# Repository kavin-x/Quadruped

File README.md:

# 🐕 In-House High-Performance Quadruped Robot

## 📌 Project Overview

This project focuses on the design and development of a **high-performance quadruped robotic dog**, built entirely in-house with a strong emphasis on modularity, efficiency, and scalability.

The system is built around custom motor control electronics using the **STM32G431CBU6** microcontroller, implementing advanced **Field Oriented Control (FOC)** and real-time **CAN FD communication** between joints.

Our goal is to design and develop every critical subsystem internally — including actuator electronics, firmware architecture, communication stack, and mechanical integration.

---

## 🎯 Objectives

- Develop high-efficiency FOC-based motor control
- Design modular smart actuators
- Implement deterministic real-time CAN FD communication
- Build scalable firmware architecture for multi-joint control
- Optimize for performance, responsiveness, and energy efficiency
- Maintain complete in-house system ownership and understanding

---

## 🧠 System Architecture

### 🔹 Control Electronics
- Microcontroller: STM32G431CBU6
- Advanced timer-based PWM generation
- Inline / low-side current sensing
- High-speed ADC sampling
- CAN FD communication interface

### 🔹 Motor Control
- Field Oriented Control (FOC)
- High switching frequency PWM
- Real-time current control loop
- Velocity and position control loops
- Optimized for low latency and high torque response

### 🔹 Communication
- CAN FD based multi-node architecture
- Deterministic joint-level communication
- Scalable bus structure for 12+ actuators
- Distributed-ready control design

### 🔹 Mechanical Design
- Modular actuator units
- Custom motor driver PCB
- Compact, serviceable architecture
- Strength-to-weight optimized structure

---

## 📂 Repository Structure
/firmware
/motor_control
/can_fd
/drivers
/middleware

/hardware
/pcb_design
/schematics
/bom

/mechanical
/cad_files
/actuator_design

/docs
/progress_reports
/architecture_notes

---

## 🚀 Current Progress

- ✅ Custom motor driver PCB designed
- ✅ STM32G431 bring-up completed
- ✅ PWM generation validated
- ✅ ADC sampling verified
- ✅ Initial FOC implementation tested
- 🔄 CAN FD communication framework in progress
- 🔄 Multi-joint synchronization under development
- 🔄 Actuator mechanical refinement ongoing

---

## 🔜 Next Steps

- Complete closed-loop position control
- Optimize FOC loop timing and stability
- Finalize CAN FD protocol structure
- Integrate multiple actuators
- Begin quadruped gait testing
- Implement high-level motion control layer

---

## 🛠️ Development Tools

- STM32CubeIDE
- STM32 HAL / LL Drivers
- Custom FOC algorithms
- Oscilloscope and logic analyzer for validation
- CAN FD debugging tools

---

## 📈 Long-Term Vision

- Fully autonomous quadruped platform
- Advanced locomotion algorithms
- Real-time state estimation
- AI-assisted gait optimization
- Expandable research and development platform

---

## 🤝 Contribution

This is currently an in-house development project.  
Documentation and structured releases will be improved progressively.

---

## 📜 License

License information will be added soon.

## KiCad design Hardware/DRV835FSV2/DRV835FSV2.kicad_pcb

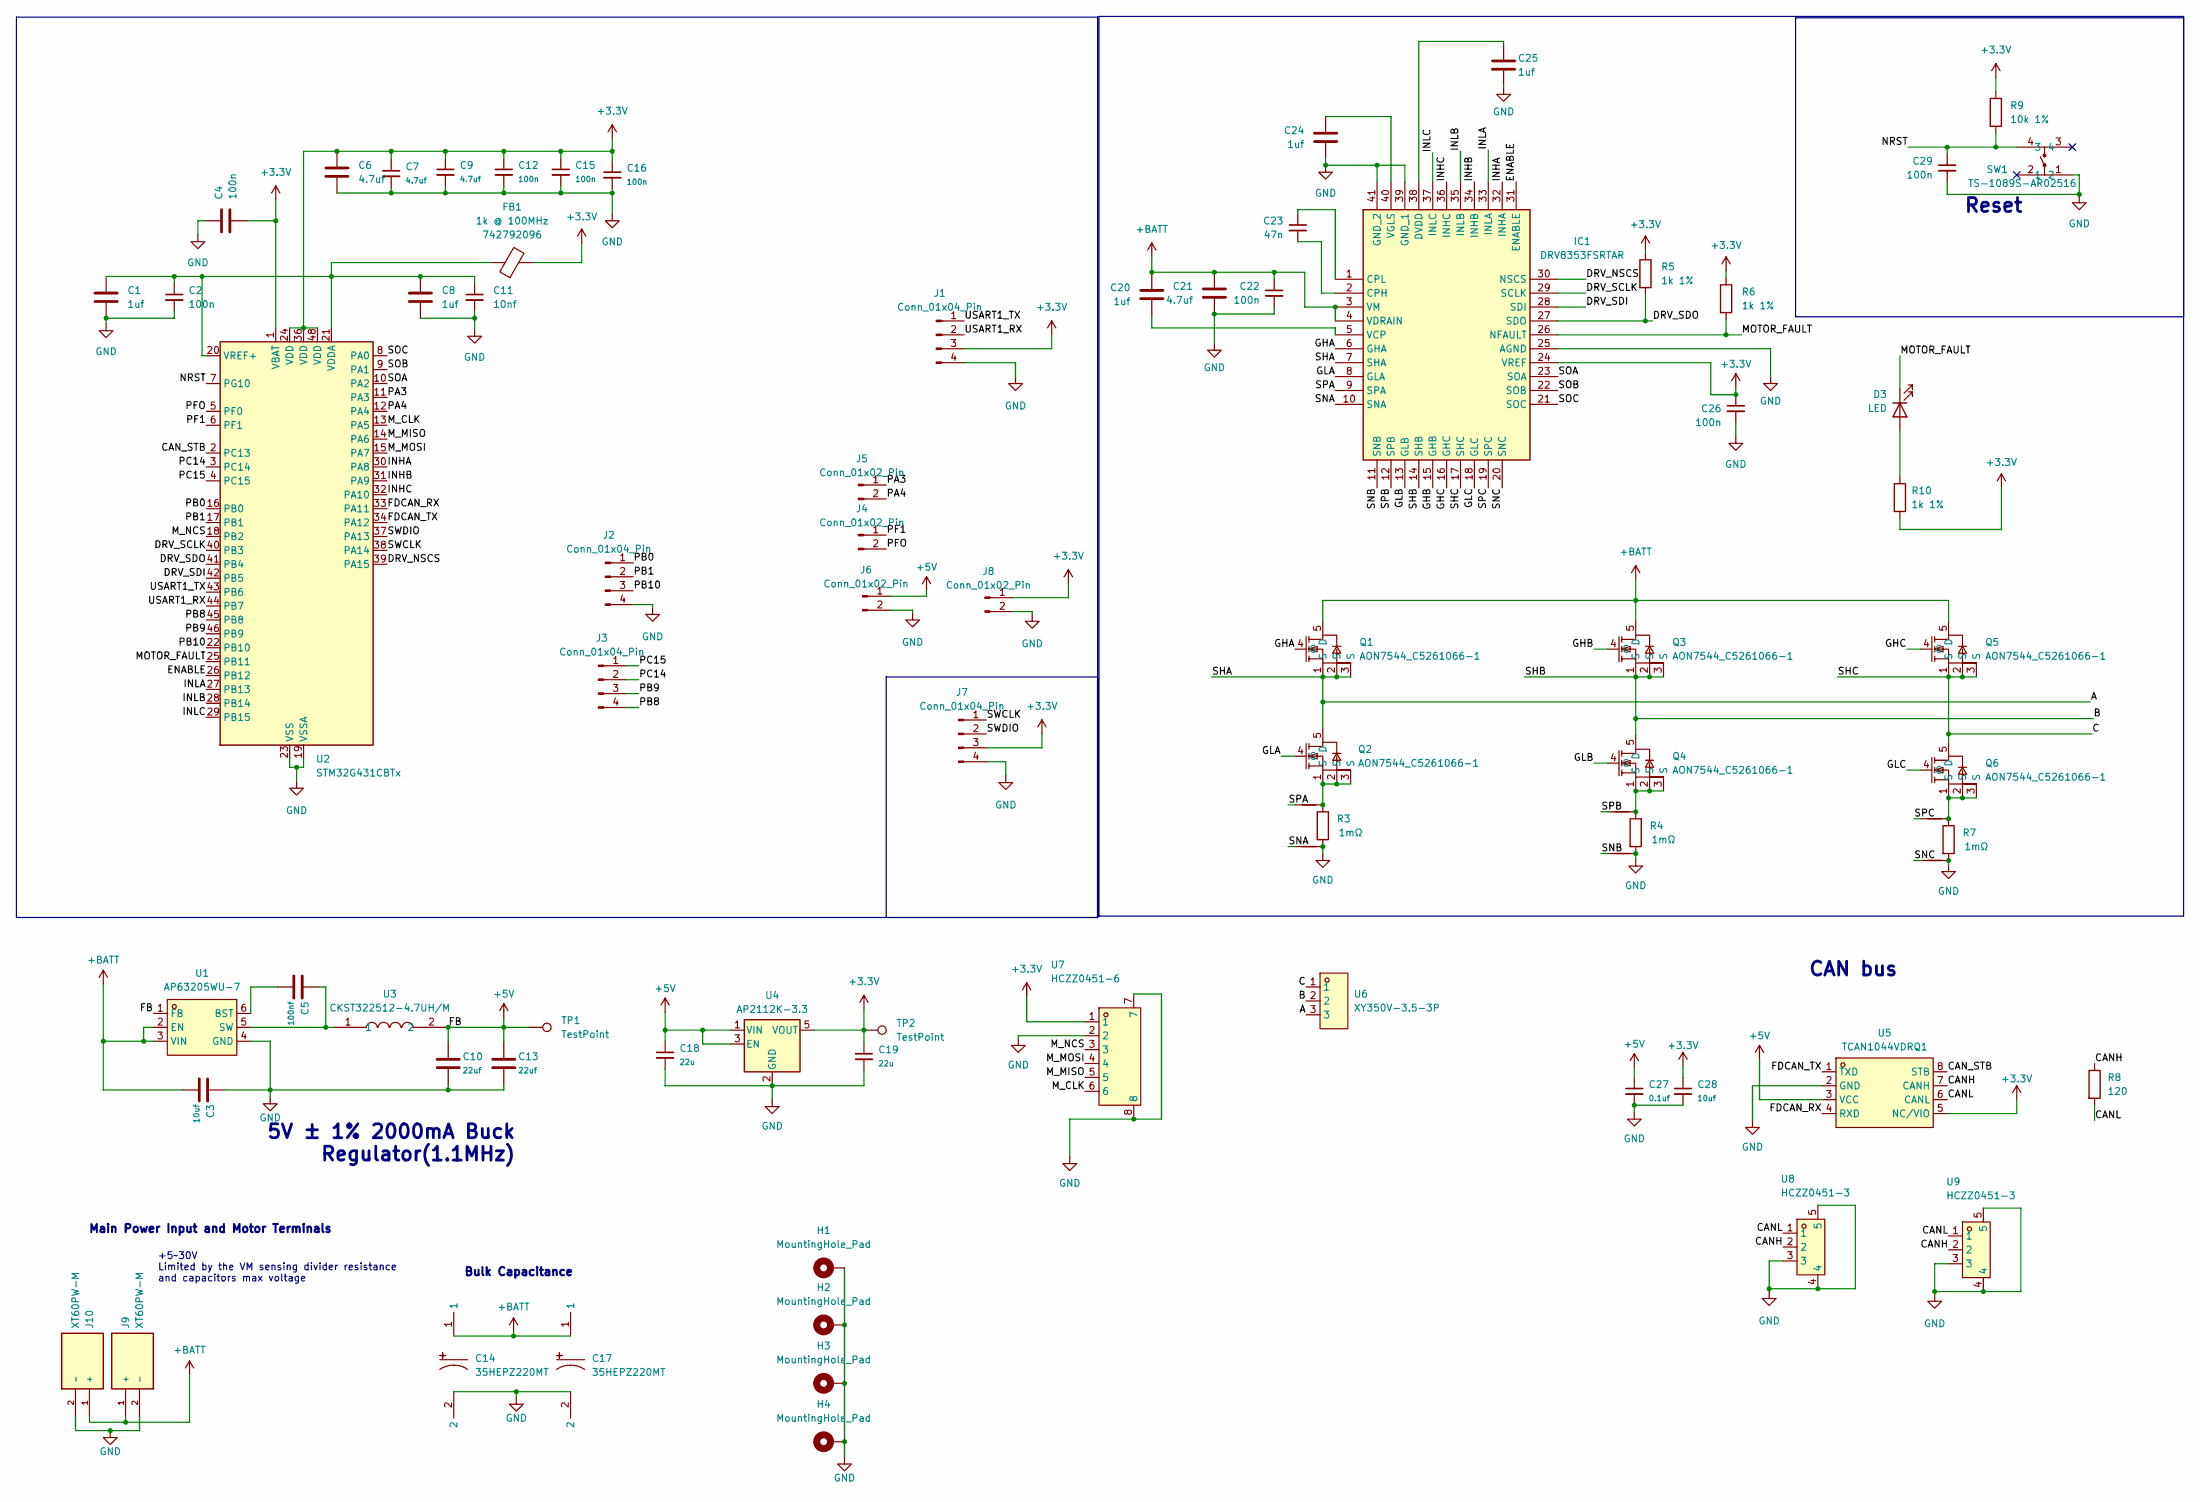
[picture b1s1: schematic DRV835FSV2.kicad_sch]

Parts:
C1: 1uf; C_0603_1608Metric; Manufacturer Part Number 04023D475MAT2A
C2, C12, C15, C16: 100n; C_0603_1608Metric; Manufacturer Part Number GCM155R71H104KE02J
C3: 10uf; C_0603_1608Metric; Manufacturer Part Number CGA4J1X7R2A225K125AC
C4: 100n; C_0603_1608Metric; Manufacturer Part Number GRM155Z71A105KE01J
C5: 100nf; C_0603_1608Metric; Manufacturer Part Number CGA4J1X7R2A225K125AC
C6: 4.7uf; C_0603_1608Metric; Manufacturer Part Number GRM188Z71C475KE21J
C7, C9: 4.7uf; C_0603_1608Metric; Manufacturer Part Number GCM155R71H104KE02J
C8: 1uf; C_0603_1608Metric; Manufacturer Part Number GRM155Z71A105KE01J
C10: 22uf; C_0603_1608Metric; Manufacturer Part Number GCM155R71H104KE02J
C11: 10nf; C_0603_1608Metric; Manufacturer Part Number GCM155R71H104KE02J
C13: 22uf; C_0603_1608Metric; Manufacturer Part Number GRM21BZ71A226ME15L
C14, C17: 35HEPZ220MT; CAP-TH_BD10.0-P5.00-D1.0-FD; LCSC Part C242064
C18, C19: 22u; C_0603_1608Metric; Manufacturer Part Number GCM155R71H104KE02J
C20, C24: 1uf; C_0603_1608Metric; Manufacturer Part Number TMK107AB7105KAHT
C21: 4.7uf; C_1206_3216Metric; Manufacturer Part Number GRJ31CZ72A475KE01L
C22: 100n; C_0603_1608Metric; Manufacturer Part Number HMK107B7104KAHT
C23: 47n; C_0603_1608Metric; Manufacturer Part Number C0603C473K1RECAUTO
C25: 1uf; C_0603_1608Metric; Manufacturer Part Number GRT155R70J105KE01D
C26: 100n; C_0603_1608Metric; Manufacturer Part Number GCM155R71C104KA55D
C27: 0.1uf; C_0603_1608Metric; Manufacturer Part Number GCM155R71H104KE02J
C28: 10uf; C_0603_1608Metric; Manufacturer Part Number GCM155R71H104KE02J
C29: 100n; C_0603_1608Metric; Manufacturer Part Number C0603C473K1RECAUTO
D3: LED; C_0603_1608Metric
FB1: 1k @ 100MHz; R_0603_1608Metric_Pad0.98x0.95mm_HandSolder; Manufacturer Part Number 742792096; LCSC Part C85824
H1, H2, H3, H4: MountingHole_Pad; MountingHole_2.7mm_Pad_Via
IC1: DRV8353FSRTAR; WQFN-40_L6.0-W6.0-P0.50-TL-EP4.5; Manufacturer_Part_Number DRV8353FSRTAR; Mouser Part Number 595-DRV8353FSRTAR
J1, J2, J3, J7: Conn_01x04_Pin; PinHeader_1x04_P2.54mm_Vertical
J4, J5, J6, J8: Conn_01x02_Pin; PinHeader_1x02_P2.54mm_Vertical
J9, J10: XT60PW-M; AMASS_XT60PW-M; PARTREV V1.2
NT1, NT2, NT3, NT4, NT5, NT6: NetTie_2; NetTie-2_SMD_Pad0.5mm
Q1, Q2, Q3, Q4, Q5, Q6: AON7544_C5261066-1; POWERDI3333-8_L3.3-W3.3-P0.65-BL; LCSC Part C5261066
R3, R4, R7: 1mΩ; R_2512_6332Metric; MFR.Part # ASR-M-3-0.5F; JLCPCB Part # C469426
R5, R6: 1k 1%; R_0603_1608Metric; Manufacturer Part Number ERJ-2RKF2001X; LCSC Part C21190
R8: 120; R_0603_1608Metric; Manufacturer Part Number ERJ-2RKF2001X; LCSC Part C21190
R9: 10k 1%; R_0603_1608Metric; Manufacturer Part Number ERJ-2RKF2001X; LCSC Part C25804
R10: 1k 1%; R_0603_1608Metric; Manufacturer Part Number ERJ-2RKF2001X; LCSC Part C25804
SW1: TS-1089S-AR02516; SW-SMD_4P-L4.2-W3.3-P2.15-LS5.1; LCSC Part C720479
TP1, TP2: TestPoint; TestPoint_Pad_D1.0mm
U1: AP63205WU-7; TSOT-23-6_L2.9-W1.6-P0.95-LS2.8-BL; LCSC Part C2071056
U2: STM32G431CBTx; LQFP-48_7x7mm_P0.5mm; LCSC Part C529355
U3: CKST322512-4.7UH/M; MGAH06034R7M-10; LCSC Part C3002560
U4: AP2112K-3.3; SOT-23-5; LCSC Part C51118
U5: TCAN1044VDRQ1; SOIC-8_L4.9-W3.9-P1.27-LS6.0-BL; LCSC Part C1852061
U6: XY350V-3.5-3P; CONN-TH_XY350V-3.5-3P; LCSC Part C557655
U7: HCZZ0451-6; CONN-SMD_HCZZ0451-6; LCSC Part C7433652
U8, U9: HCZZ0451-3; CONN-SMD_3P-P2.00_HCZZ0451-3_1; LCSC Part C7433649

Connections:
+3.3V: C4.2, C6.1, C7.1, C9.1, C12.1, C15.1, C16.1, C19.1, C26.1, C28.1, FB1.2, IC1.24 (VREF), J1.3, J7.3, J8.1, R5.1, R6.1, R9.1, R10.2, TP2.1, U2.1 (VBAT), U2.24 (VDD), U2.36 (VDD), U2.48 (VDD), U4.5 (VOUT), U5.5 (NC/VIO), U7.1
+5V: C10.1, C13.1, C18.1, C27.1, J6.1, TP1.1, U1.1 (FB), U3.2, U4.1 (VIN), U4.3 (EN), U5.3 (VCC)
+BATT: C3.2, C14.1, C17.1, C20.1, C21.1, C22.1, IC1.3 (VM), IC1.4 (VDRAIN), J9.1 (+), J10.1 (+), Q1.5 (D), Q3.5 (D), Q5.5 (D), U1.2 (EN), U1.3 (VIN)
/A: IC1.7 (SHA), Q1.1 (S), Q1.2 (S), Q1.3 (S), Q2.5 (D), U6.3
/B: IC1.14 (SHB), Q3.1 (S), Q3.2 (S), Q3.3 (S), Q4.5 (D), U6.2
/C: IC1.17 (SHC), Q5.1 (S), Q5.2 (S), Q5.3 (S), Q6.5 (D), U6.1
/CANH: R8.1, U5.7 (CANH), U8.2, U9.2
/CANL: R8.2, U5.6 (CANL), U8.1, U9.1
/CAN_STB: U2.2 (PC13), U5.8 (STB)
/DRV_NSCS: IC1.30 (NSCS), U2.39 (PA15)
/DRV_SCLK: IC1.29 (SCLK), U2.40 (PB3)
/DRV_SDI: IC1.28 (SDI), U2.42 (PB5)
/DRV_SDO: IC1.27 (SDO), R5.2, U2.41 (PB4)
/ENABLE: IC1.31 (ENABLE), U2.26 (PB12)
/FDCAN_RX: U2.33 (PA11), U5.4 (RXD)
/FDCAN_TX: U2.34 (PA12), U5.1 (TXD)
/GHA: IC1.6 (GHA), Q1.4 (G)
/GHB: IC1.15 (GHB), Q3.4 (G)
/GHC: IC1.16 (GHC), Q5.4 (G)
/GLA: IC1.8 (GLA), Q2.4 (G)
/GLB: IC1.13 (GLB), Q4.4 (G)
/GLC: IC1.18 (GLC), Q6.4 (G)
/INHA: IC1.32 (INHA), U2.30 (PA8)
/INHB: IC1.34 (INHB), U2.31 (PA9)
/INHC: IC1.36 (INHC), U2.32 (PA10)
/INLA: IC1.33 (INLA), U2.27 (PB13)
/INLB: IC1.35 (INLB), U2.28 (PB14)
/INLC: IC1.37 (INLC), U2.29 (PB15)
/MOTOR_FAULT: D3.1 (K), IC1.26 (NFAULT), R6.2, U2.25 (PB11)
/M_CLK: U2.13 (PA5), U7.6
/M_MISO: U2.14 (PA6), U7.5
/M_MOSI: U2.15 (PA7), U7.4
/M_NCS: U2.18 (PB2), U7.3
/NRST: C29.1, R9.2, SW1.4, U2.7 (PG10)
/PA3: J5.1, U2.11 (PA3)
/PA4: J5.2, U2.12 (PA4)
/PB0: J2.1, U2.16 (PB0)
/PB1: J2.2, U2.17 (PB1)
/PB8: J3.4, U2.45 (PB8)
/PB9: J3.3, U2.46 (PB9)
/PB10: J2.3, U2.22 (PB10)
/PC14: J3.2, U2.3 (PC14)
/PC15: J3.1, U2.4 (PC15)
/PF1: J4.1, U2.6 (PF1)
/PFO: J4.2, U2.5 (PF0)
/SNA: IC1.10 (SNA), NT2.1
/SNB: IC1.11 (SNB), NT4.1
/SNC: IC1.20 (SNC), NT6.1
/SOA: IC1.23 (SOA), U2.10 (PA2)
/SOB: IC1.22 (SOB), U2.9 (PA1)
/SOC: IC1.21 (SOC), U2.8 (PA0)
/SPA: IC1.9 (SPA), NT1.1
/SPB: IC1.12 (SPB), NT3.1
/SPC: IC1.19 (SPC), NT5.1
/SWCLK: J7.1, U2.38 (PA14)
/SWDIO: J7.2, U2.37 (PA13)
/USART1_RX: J1.2, U2.44 (PB7)
/USART1_TX: J1.1, U2.43 (PB6)
GND: C1.2, C2.2, C3.1, C4.1, C6.2, C7.2, C8.2, C9.2, C10.2, C11.2, C12.2, C13.2, C14.2, C15.2, C16.2, C17.2, C18.2, C19.2, C21.2, C22.2, C24.2, C25.2, C26.2, C27.2, C28.2, C29.2, H1.1, H2.1, H3.1, H4.1, IC1.25 (AGND), IC1.39 (GND_1), IC1.41 (GND_2), J1.4, J2.4, J6.2, J7.4, J8.2, J9.2 (-), J10.2 (-), NT2.2, NT4.2, NT6.2, R3.2, R4.2, R7.2, SW1.1, U1.4 (GND), U2.19 (VSSA), U2.23 (VSS), U2.35 (VSS), U2.47 (VSS), U4.2 (GND), U5.2 (GND), U7.2, U7.7, U7.8, U8.3, U8.4, U8.5, U9.3, U9.4, U9.5
unnamed: D3.2 (A), R10.1
unnamed: C23.2, IC1.2 (CPH)
unnamed: C23.1, IC1.1 (CPL)
unnamed: C25.1, IC1.38 (DVDD)
unnamed: C20.2, IC1.5 (VCP)
unnamed: C24.1, IC1.40 (VGLS)
unnamed: NT1.2, Q2.1 (S), Q2.2 (S), Q2.3 (S), R3.1
unnamed: NT3.2, Q4.1 (S), Q4.2 (S), Q4.3 (S), R4.1
unnamed: NT5.2, Q6.1 (S), Q6.2 (S), Q6.3 (S), R7.1
unnamed: C5.2, U1.6 (BST)
unnamed: C5.1, U1.5 (SW), U3.1
unnamed: C1.1, C2.1, C8.1, C11.1, FB1.1, U2.20 (VREF+), U2.21 (VDDA)

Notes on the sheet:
Reset
CAN bus
5V ± 1% 2000mA Buck Regulator(1.1MHz)
+5~30V Limited by the VM sensing divider resistance and capacitors max voltage
Main Power Input and Motor Terminals
Bulk Capacitance

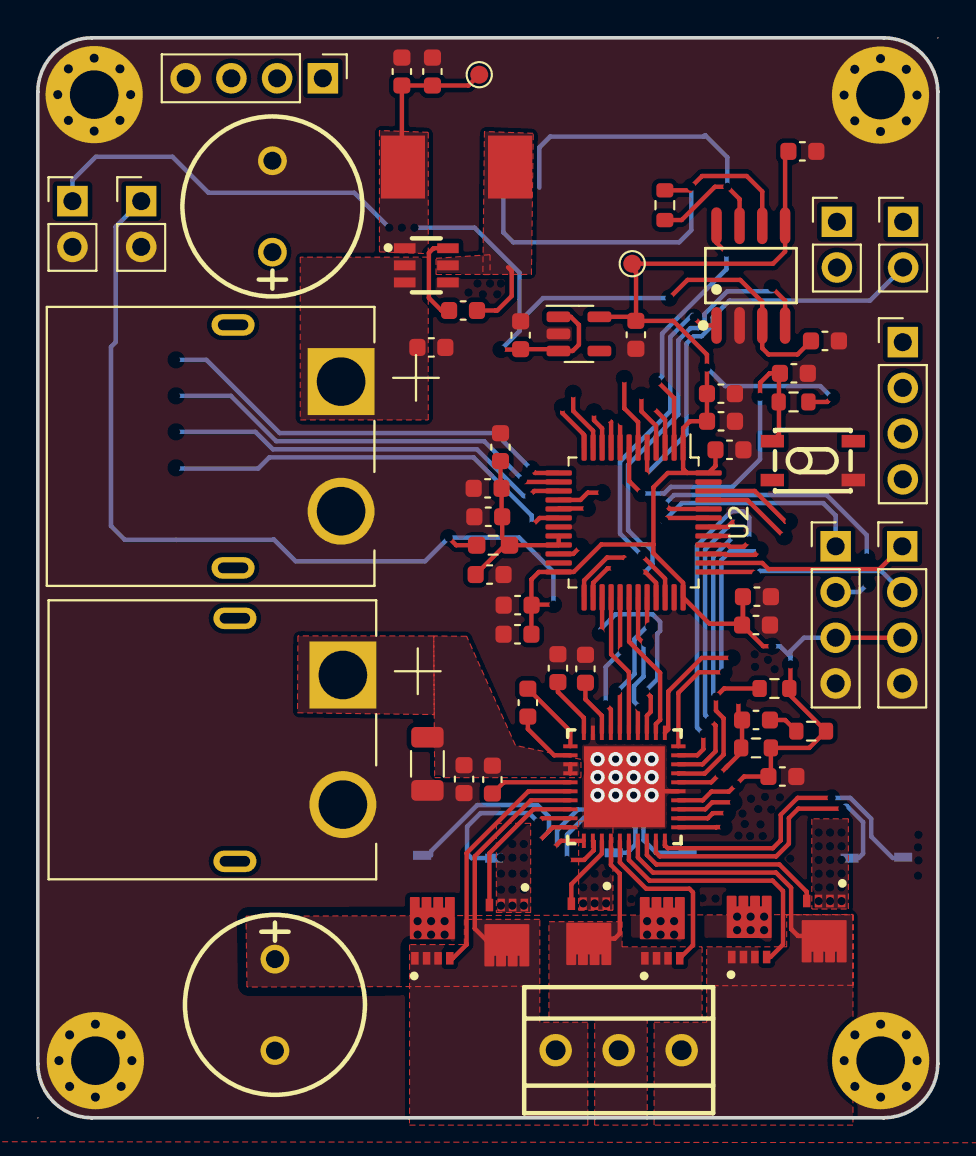
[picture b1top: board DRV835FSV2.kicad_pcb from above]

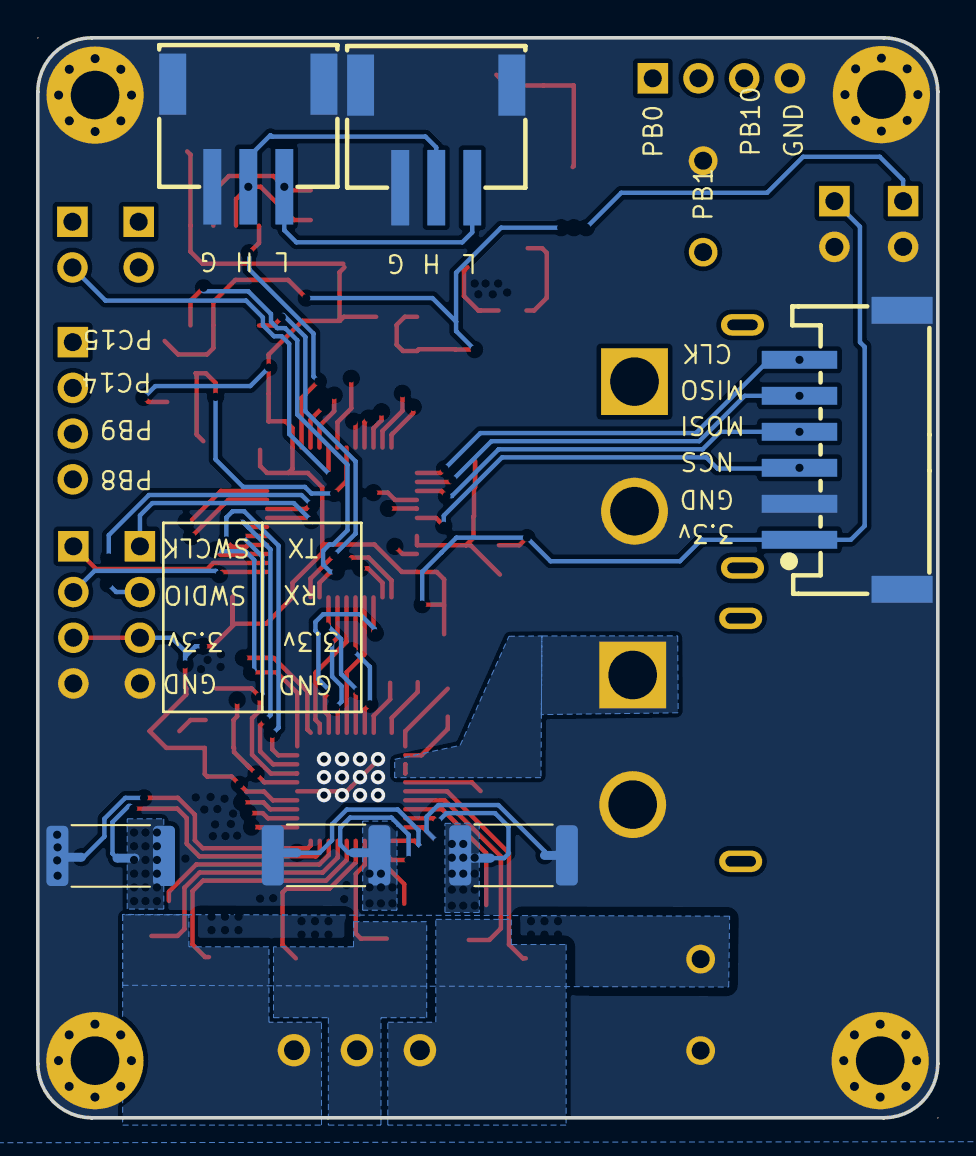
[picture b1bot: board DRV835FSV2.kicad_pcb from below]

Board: 4 copper layers, 50.0 x 60.0 mm, 78 parts (12 on the bottom side), 71 nets.

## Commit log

2026-03-04 Init
